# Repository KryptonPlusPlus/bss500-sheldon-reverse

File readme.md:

# Sheldon BSS500 — Reverse Engineering

Engenharia reversa do amplificador de áudio **Sheldon BSS500**, com o objetivo de reconstruir seu circuito, documentar seus componentes e explorar possíveis modificações e melhorias.

> [!WARNING]
> **Atenção:** As informações deste repositório são baseadas na análise de um amplificador que aparenta ter passado por manutenções ou modificações anteriores. Portanto, alguns valores de componentes e conexões podem diferir do projeto original de fábrica. As informações documentadas são preliminares e devem ser verificadas antes de qualquer reprodução ou montagem do circuito.

## Objetivos

- Reconstruir o esquemático eletrônico a partir do equipamento físico.
- Identificar e documentar os componentes utilizados.
- Registrar as conexões e o funcionamento dos estágios do amplificador.
- Investigar possíveis modificações e melhorias no circuito.
- Documentar as alterações realizadas e seus efeitos no funcionamento do equipamento.

## Modificações e melhorias

Além da reconstrução do circuito, o projeto poderá incluir modificações com fins de estudo, aprimoramento e experimentação.

As possíveis alterações serão avaliadas conforme o avanço da análise do circuito original, considerando aspectos como desempenho, estabilidade, confiabilidade e qualidade de áudio.

## Status do projeto

O projeto está em desenvolvimento. A reconstrução do esquemático, a identificação dos componentes e a avaliação de possíveis modificações serão realizadas progressivamente.

## Disclaimer

Este é um projeto independente de engenharia reversa, desenvolvido para fins de estudo, experimentação e documentação. Não se trata de documentação oficial do fabricante Sheldon.

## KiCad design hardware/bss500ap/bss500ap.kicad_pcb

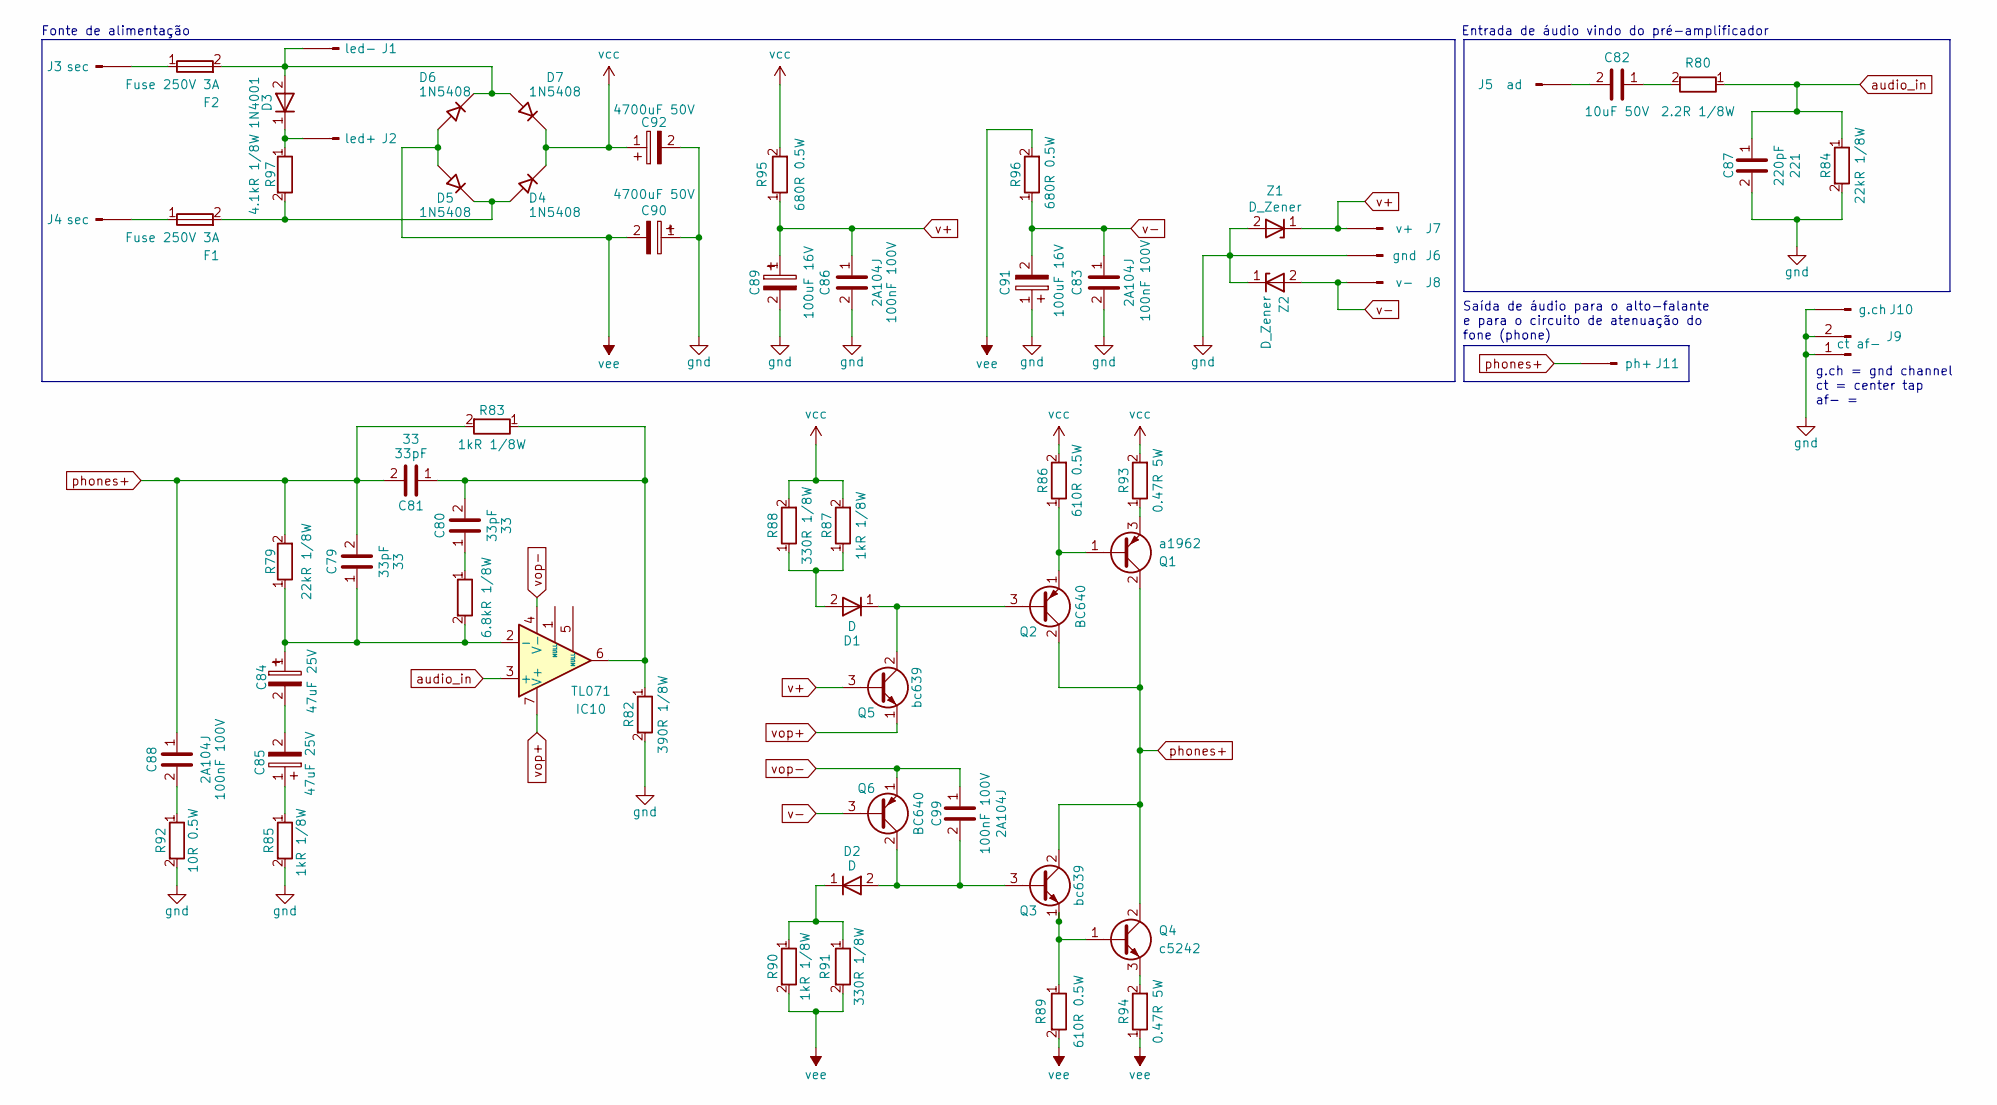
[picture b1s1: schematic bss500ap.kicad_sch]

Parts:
C79: 33pF; C_Disc_D7.5mm_W5.0mm_P7.50mm
C80, C81: 33pF; C_Disc_D4.3mm_W1.9mm_P5.00mm
C82: 10uF 50V; C_Radial_D6.3mm_H11.0mm_P2.50mm
C83, C86, C88, C99: 100nF 100V; C_Rect_L10.0mm_W4.0mm_P7.50mm_MKS4
C84, C85: 47uF 25V; CP_Radial_D5.0mm_P2.50mm
C87: 220pF; C_Disc_D6.0mm_W2.5mm_P5.00mm
C89: 100uF 16V; CP_Radial_D5.0mm_P2.50mm
C90, C92: 4700uF 50V; CP_Radial_D18.0mm_P7.50mm
C91: 100uF 16V; CP_Radial_D10.0mm_P5.00mm
D1, D2: D; D_T-1_P5.08mm_Horizontal
D3: 1N4001; D_DO-41_SOD81_P10.16mm_Horizontal
D4, D5, D6, D7: 1N5408; D_DO-201AE_P5.08mm_Vertical_KathodeUp
F1, F2: Fuse 250V 3A; Fuseholder_Cylinder-5x20mm_Schurter_0031_8201_Horizontal_Op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
IC10: TL071; DIP-8_W7.62mm_LongPads
J1: led-; PinHeader_1x01_P2.54mm_Vertical
J2: led+; PinHeader_1x01_P2.54mm_Vertical
J3, J4: sec; PinHeader_1x01_P2.54mm_Vertical
J5: ad; PinHeader_1x01_P2.54mm_Vertical
J6: gnd; PinHeader_1x01_P2.54mm_Vertical
J7: v+; PinHeader_1x01_P2.54mm_Vertical
J8: v-; PinHeader_1x01_P2.54mm_Vertical
J9: ct af-; PinHeader_1x02_P2.54mm_Vertical
J10: g.ch; PinHeader_1x01_P2.54mm_Vertical
J11: ph+; PinHeader_1x01_P2.54mm_Vertical
Q1: a1962; PinHeader_1x03_P2.54mm_Vertical
Q2, Q6: BC640; TO-92_Inline_Wide
Q3, Q5: bc639; TO-92_Inline_Wide
Q4: c5242; PinHeader_1x03_P2.54mm_Vertical
R79, R84: 22kR 1/8W; R_Axial_DIN0204_L3.6mm_D1.6mm_P7.62mm_Horizontal
R80: 2.2R 1/8W; R_Axial_DIN0204_L3.6mm_D1.6mm_P7.62mm_Horizontal
R81: 6.8kR 1/8W; R_Axial_DIN0204_L3.6mm_D1.6mm_P7.62mm_Horizontal
R82: 390R 1/8W; R_Axial_DIN0204_L3.6mm_D1.6mm_P7.62mm_Horizontal
R83, R85, R87, R90: 1kR 1/8W; R_Axial_DIN0204_L3.6mm_D1.6mm_P7.62mm_Horizontal
R86, R89: 610R 0.5W; R_Axial_DIN0207_L6.3mm_D2.5mm_P10.16mm_Horizontal
R88, R91: 330R 1/8W; R_Axial_DIN0204_L3.6mm_D1.6mm_P7.62mm_Horizontal
R92: 10R 0.5W; R_Axial_DIN0207_L6.3mm_D2.5mm_P10.16mm_Horizontal
R93, R94: 0.47R 5W; R_Axial_DIN0207_L6.3mm_D2.5mm_P15.24mm_Horizontal
R95, R96: 680R 0.5W; R_Axial_DIN0207_L6.3mm_D2.5mm_P10.16mm_Horizontal
R97: 4.1kR 1/8W; R_Axial_DIN0207_L6.3mm_D2.5mm_P10.16mm_Horizontal
Z1, Z2: D_Zener; D_DO-34_SOD68_P7.62mm_Horizontal

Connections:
unnamed: C80.1, R81.1
unnamed: C80.2, C81.1, IC10.6, R82.1, R83.1
unnamed: C82.1, R80.2
unnamed: C84.2, C85.2
unnamed: C85.1, R85.1
unnamed: C88.2, R92.1
unnamed: D1.2 (A), R87.1, R88.1
unnamed: D1.1 (K), Q2.3 (B), Q5.2 (C)
unnamed: C99.2, D2.2 (A), Q3.3 (B), Q6.2 (C)
unnamed: D2.1 (K), R90.1, R91.1
unnamed: D3.2 (A), D6.1 (K), D7.2 (A), F2.2, J1.1
unnamed: D3.1 (K), J2.1, R97.1
unnamed: D4.2 (A), D5.1 (K), F1.2, R97.2
unnamed: C79.1, C84.1, IC10.2 (-), R79.1, R81.2
unnamed: F2.1, J3.1
unnamed: F1.1, J4.1
unnamed: C82.2, J5.1
unnamed: Q1.1 (B), Q2.1 (E), R86.1
unnamed: Q1.3 (E), R93.1
unnamed: Q3.1 (E), Q4.1 (B), R89.1
unnamed: Q4.3 (E), R94.2
audio_in: C87.1, IC10.3 (+), R80.1, R84.1
gnd: C83.2, C86.2, C87.2, C89.2, C90.1, C91.1, C92.2, J6.1, J9.1, J9.2, J10.1, R82.2, R84.2, R85.2, R92.2, Z1.2 (A), Z2.1 (K)
phones+: C79.2, C81.2, C88.1, J11.1, Q1.2 (C), Q2.2 (C), Q3.2 (C), Q4.2 (C), R79.2, R83.2
v+: C86.1, C89.1, J7.1, Q5.3 (B), R95.1, Z1.1 (K)
v-: C83.1, C91.2, J8.1, Q6.3 (B), R96.1, Z2.2 (A)
vcc: C92.1, D4.1 (K), D7.1 (K), R86.2, R87.2, R88.2, R93.2, R95.2
vee: C90.2, D5.2 (A), D6.2 (A), R89.2, R90.2, R91.2, R94.1, R96.2
vop+: IC10.7 (V+), Q5.1 (E)
vop-: C99.1, IC10.4 (V-), Q6.1 (E)

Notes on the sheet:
Entrada de áudio vindo do pré-amplificador
Saída de áudio para o alto-falante e para o circuito de atenuação do fone (phone)
Fonte de alimentação
g.ch = gnd channel ct = center tap af- =

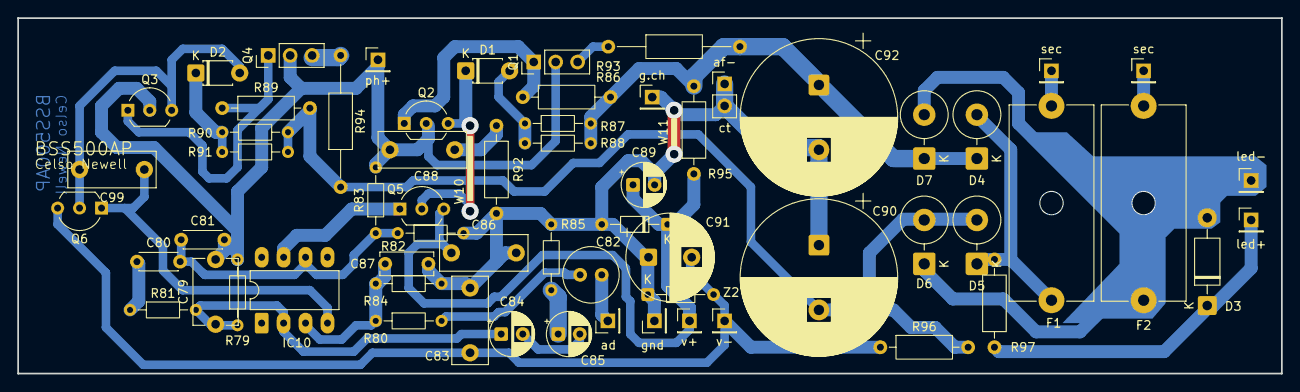
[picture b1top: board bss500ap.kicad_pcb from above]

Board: 2 copper layers, 146.3 x 41.1 mm, 63 parts (0 on the bottom side), 30 nets.

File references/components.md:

# Componentes do Amplificador

Lista de Materiais para a PCB bss500ap do amplificador Sheldon BSS500.

> **Note:** Esta lista abrange apenas a PCB do amplificador. Os valores dos componentes e as suas respectivas *footprints* baseiam-se em um projeto obtido por engenharia reversa e podem diferir do projeto original de fábrica.

## Capacitores

| Referência | Quantidade  | Valor | Footprint |
|---|---:|---|---|
| C79 | 1 | 33pF | `Capacitor_THT:C_Disc_D7.5mm_W5.0mm_P7.50mm` |
| C80, C81 | 2 | 33pF | `Capacitor_THT:C_Disc_D4.3mm_W1.9mm_P5.00mm` |
| C82 | 1 | 10uF 50V | `Capacitor_THT:C_Radial_D6.3mm_H11.0mm_P2.50mm` |
| C83, C86, C88, C99 | 4 | 100nF 100V | `Capacitor_THT:C_Rect_L10.0mm_W4.0mm_P7.50mm_MKS4` |
| C84, C85 | 2 | 47uF 25V | `Capacitor_THT:CP_Radial_D5.0mm_P2.50mm` |
| C87 | 1 | 220pF | `Capacitor_THT:C_Disc_D6.0mm_W2.5mm_P5.00mm` |
| C89 | 1 | 100uF 16V | `Capacitor_THT:CP_Radial_D5.0mm_P2.50mm` |
| C90, C92 | 2 | 4700uF 50V | `Capacitor_THT:CP_Radial_D18.0mm_P7.50mm` |
| C91 | 1 | 100uF 16V | `Capacitor_THT:CP_Radial_D10.0mm_P5.00mm` |

## Diodos

| Referência | Quantidade  | Valor | Footprint
|---|---:|---|---|
| D1, D2 | 2 | D | `Diode_THT:D_T-1_P5.08mm_Horizontal` |
| D3 | 1 | 1N4001 | `Diode_THT:D_DO-41_SOD81_P10.16mm_Horizontal` |
| D4, D5, D6, D7 | 4 | 1N5408 | `Diode_THT:D_DO-201AE_P5.08mm_Vertical_KathodeUp` |
| Z1, Z2 | 2 | D_Zener | `Diode_THT:D_DO-34_SOD68_P7.62mm_Horizontal` |

## fusíveis

| Referência | Quantidade  | Valor | Footprint |
|---|---:|---|---|
| F1, F2 | 2 | Fuse 250V 3A | `Fuse:Fuseholder_Cylinder-5x20mm_Schurter_0031_8201_Horizontal_Open` |

## Circuitos integrados

| Referência | Quantidade  | Valor | Footprint |
|---|---:|---|---|
| IC10 | 1 | TL071 | `Package_TO_SOT_THT:TO-3P-3_Vertical` |

## Transistores

| Referência | Quantidade  | Valor | Footprint |
|---|---:|---|---|
| Q1 | 1 | a1962 | `Package_TO_SOT_THT:TO-3P-3_Vertical` |
| Q2, Q6 | 2 | BC640 | `Package_TO_SOT_THT:TO-92_Inline_Wide` |
| Q3, Q5 | 2 | bc639 | `Package_TO_SOT_THT:TO-92_Inline_Wide` |
| Q4 | 1 | c5242 | `Package_TO_SOT_THT:TO-3P-3_Vertical` |

## Resistores

| Referência | Quantidade | Valor | Footprint |
|---|---:|---|---|
| R79, R84 | 2 | 22kR 1/8W | `Resistor_THT:R_Axial_DIN0204_L3.6mm_D1.6mm_P7.62mm_Horizontal` |
| R80 | 1 | 2.2R 1/8W | `Resistor_THT:R_Axial_DIN0204_L3.6mm_D1.6mm_P7.62mm_Horizontal` |
| R81 | 1 | 6.8kR 1/8W | `Resistor_THT:R_Axial_DIN0204_L3.6mm_D1.6mm_P7.62mm_Horizontal` |
| R82 | 1 | 390R 1/8W | `Resistor_THT:R_Axial_DIN0204_L3.6mm_D1.6mm_P7.62mm_Horizontal` |
| R83, R85, R87, R90 | 4 | 1kR 1/8W | `Resistor_THT:R_Axial_DIN0204_L3.6mm_D1.6mm_P7.62mm_Horizontal` |
| R86, R89 | 2 | 610R 0.5W | `Resistor_THT:R_Axial_DIN0207_L6.3mm_D2.5mm_P10.16mm_Horizontal` |
| R88, R91 | 2 | 330R 1/8W | `Resistor_THT:R_Axial_DIN0204_L3.6mm_D1.6mm_P7.62mm_Horizontal` |
| R92 | 1 | 10R 0.5W | `Resistor_THT:R_Axial_DIN0207_L6.3mm_D2.5mm_P10.16mm_Horizontal` |
| R93, R94 | 2 | 0.47R 5W | `Resistor_THT:R_Axial_DIN0207_L6.3mm_D2.5mm_P15.24mm_Horizontal` |
| R95, R96 | 2 | 680R 0.5W | `Resistor_THT:R_Axial_DIN0207_L6.3mm_D2.5mm_P10.16mm_Horizontal` |
| R97 | 1 | 4.1kR 1/8W | `Resistor_THT:R_Axial_DIN0207_L6.3mm_D2.5mm_P10.16mm_Horizontal` |
